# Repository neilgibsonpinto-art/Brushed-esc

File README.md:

# STMESC - Dual-Motor Brushed Electronic Speed Controller

[-green.svg)](https://www.st.com)
[-orange.svg)](#power-specifications)

**STMESC** is an open-source, high-power dual-channel electronic speed controller designed to drive **two DC brushed motors independently** (up to 15 A per channel) from a **3S to 6S LiPo battery (9.0 V – 25.2 V)**. 

Powered by a **240 MHz dual-core ESP32**, the STMESC features **Tri-Mode Hybrid Control** (Bluetooth LE, Wi-Fi, and standard hobby RC), onboard reverse polarity protection, real-time current sensing with stall detection, and an integrated 5 V / 2 A switching BEC. It is ideally suited for combat robotics, differential-drive rovers, smart RC models, and automation platforms.

---

## 📸 Hardware Previews

<div align="center">
  
  &nbsp;
  
</div>

---

## 🌟 Key Features

* **Dual Independent 15 A H-Bridges**: Dual automotive-grade **STMicroelectronics VNH7070BASTR** drivers with integrated power MOSFETs, charge pumps, and diagnostic logic.
* **3S to 6S LiPo Voltage Range ($9.0\text{ V} - 25.2\text{ V}$)**: Wide input voltage support compatible with 3S ($11.1\text{ V}$), 4S ($14.8\text{ V}$), and 6S ($22.2\text{ V}$) packs.
* **Ultrasonic PWM Drive**: Hardware PWM up to $20\text{ kHz}$ for smooth, responsive, and completely silent motor operation (no high-pitch whine).
* **Tri-Mode Hybrid Connectivity**:
  1. **Bluetooth Low Energy (BLE)**: Low-latency smartphone and gamepad control with live telemetry.
  2. **Wi-Fi Web Dashboard**: Built-in access point and HTTP/WebSocket server for control from any browser without installing an app.
  3. **RC Receiver Input**: Direct hardware pulse decoding for FlySky, FrSky, RadioMaster, ELRS, and Spektrum transmitters.
* **Real-Time Current Sensing & Stall Protection**: Dedicated ST MultiSense current feedback ($K_{sense} \approx 2000$) on both channels for active stall detection and overcurrent limiting.
* **Active Reverse Polarity Protection**: Low-$R_{DS(on)}$ P-Channel MOSFET with Zener gate clamp prevents board destruction if battery leads are reversed.
* **Integrated Dual Power Supply**:
  - **$5.0\text{ V} \text{ @ } 2.0\text{ A}$ Synchronous Buck Converter** (`U6`: AP63205) powers external receivers and sensors.
  - **$3.3\text{ V} \text{ @ } 1.0\text{ A}$ Low-Dropout Linear Regulator** (`U5`: AMS1117-3.3) powers the ESP32 and logic circuitry.
* **Developer & Maker Friendly**: Standard 6-pin UART programming header with auto-bootloader control, on-board tactile buttons (Reset, Boot, Mode), and diagnostic status LEDs.

---

## 📐 System Architecture

```mermaid
flowchart TD
    subgraph PowerStage ["Power Management (3S-6S LiPo: 9V - 25.2V)"]
        BAT["Battery Input J5\n(5.08mm Terminal)"] --> RP["Reverse Polarity Protection\n(Q2 P-MOSFET + D3 15V Zener)"]
        RP --> VCC["Main Rail (VCC: 9V - 25.2V)"]
        VCC --> BUCK["5V 2A Buck Regulator\n(U6: AP63205)"]
        BUCK --> LDO["3.3V 1A LDO Regulator\n(U5: AMS1117-3.3)"]
    end

    subgraph MCU ["Controller Brain (ESP32-WROOM-32E)"]
        LDO --> ESP["ESP32 Dual-Core @ 240MHz"]
        SW["Mode Select Switch (SW3)"] --> ESP
        LEDS["Status LEDs (D1, D4, D5)"] <-- ESP
    end

    subgraph Inputs ["Tri-Mode Control Inputs"]
        BLE["Mode 1: Bluetooth LE\n(Phone App / Gamepad)"] -.-> ESP
        WIFI["Mode 2: Wi-Fi\n(Web Dashboard / Telemetry)"] -.-> ESP
        RC["Mode 3: RC Receiver Header J6\n(Dual Channel PWM / PPM)"] --> ESP
    end

    subgraph MotorDrivers ["Dual ST VNH7070BASTR Drivers"]
        VCC --> U1["Driver 1: Motor 1 (U1)"]
        VCC --> U2["Driver 2: Motor 2 (U2)"]
        
        ESP -- "PWM1, INA1, INB1" --> U1
        ESP -- "PWM2, INA2, INB2" --> U2
        
        U1 -- "MultiSense Current" --> CS1["Current Filter (ADC1_CH1)"] --> ESP
        U2 -- "MultiSense Current" --> CS2["Current Filter (ADC1_CH2)"] --> ESP
        
        U1 --> M1["Motor 1 Output (J2)"]
        U2 --> M2["Motor 2 Output (J3)"]
    end
```

---

## 🔌 Pinout & Connector Specifications

### Power & Motor Terminals (5.08 mm Screw Blocks)
| Connector | Pin | Net Name | Description |
| :--- | :---: | :--- | :--- |
| **`J5`** | 1 | `VABT` | Battery Positive Input ($+9.0\text{ V}$ to $+25.2\text{ V}$) |
| | 2 | `GND` | Battery Negative / Power Ground |
| **`J2`** | 1, 2 | `Net-(J2-Pin_1)`, `Net-(J2-Pin_2)` | Motor 1 Phase Outputs (Bi-directional, up to 15 A) |
| **`J3`** | 1, 2 | `Net-(J3-Pin_1)`, `Net-(J3-Pin_2)` | Motor 2 Phase Outputs (Bi-directional, up to 15 A) |

### Control & Interface Headers
| Header | Pin | Signal | ESP32 GPIO | Description |
| :--- | :---: | :--- | :---: | :--- |
| **`J4` (UART)** | 1 | `+3V3` | - | 3.3 V Power (from onboard LDO) |
| | 2 | `/MCU_TXD` | GPIO1 | ESP32 UART0 Transmit |
| | 3 | `/MCU_RXD` | GPIO3 | ESP32 UART0 Receive |
| | 4 | `/MCU_IO0` | GPIO0 | Bootloader strapping pin (active LOW) |
| | 5 | `/MCU_EN` | EN | Microcontroller Enable / Reset (active LOW) |
| | 6 | `GND` | GND | Logic Ground |
| **`J6` (RC In)** | 1 | `/RC_IN1` | GPIO18 | Channel 1 RC pulse input (Throttle / Motor 1) |
| | 2 | `/RC_IN2` | GPIO16 | Channel 2 RC pulse input (Steering / Motor 2) |
| | 3, 4 | `+5V` | - | $+5.0\text{ V}$ BEC Output (powers external RC receiver) |
| | 5, 6 | `GND` | - | Receiver Ground |

### Tactile Switches & Status Indicators
| Component | Connected To | Function |
| :--- | :--- | :--- |
| **`SW1`** | `EN` / Reset | Hardware reset push button |
| **`SW2`** | `GPIO0` / Boot | Firmware flash bootloader button |
| **`SW3`** | `GPIO4` | Control Mode cycle switch (BLE $\leftrightarrow$ Wi-Fi $\leftrightarrow$ RC) |
| **`D1`** | `GPIO23` | Status Indicator LED 1 |
| **`D4`** | `GPIO21` | Mode Indicator LED 2 |
| **`D5`** | `GPIO22` | Fault / Diagnostic Alert LED 3 |

---

## 🕹️ Motor Truth Table

The ESP32 controls the ST VNH7070 drivers using **`INA`**, **`INB`**, and **`PWM`** logic signals:

| State | INA | INB | PWM | OUTA | OUTB | Motor Action |
| :--- | :---: | :---: | :---: | :---: | :---: | :--- |
| **Forward** | **HIGH** | **LOW** | **PWM %** | $V_{CC}$ (Chopped) | GND | Motor rotates forward; speed proportional to PWM duty cycle |
| **Reverse** | **LOW** | **HIGH** | **PWM %** | GND | $V_{CC}$ (Chopped) | Motor rotates reverse; speed proportional to PWM duty cycle |
| **Brake** | **LOW** | **LOW** | **HIGH** | GND | GND | Dynamic braking: low-side FETs short motor back-EMF |
| **Coast** | **LOW** | **LOW** | **LOW** | High-Z | High-Z | All MOSFETs disabled; motor freewheels to a stop |

---

## 📊 Technical Specifications

| Parameter | Specification |
| :--- | :--- |
| **PCB Form Factor** | $55.0\text{ mm} \times 45.0\text{ mm}$ (2-Layer FR-4, $1.6\text{ mm}$ thickness) |
| **Nominal Input Voltage** | $9.0\text{ V} - 25.2\text{ V}$ (3S, 4S, 5S, 6S LiPo / Li-ion) |
| **Max Continuous Current** | 10 A – 15 A peak per motor channel |
| **BEC Output** | $5.0\text{ V} \text{ @ } 2.0\text{ A}$ (Synchronous Step-Down Buck) |
| **Logic Voltage** | $3.3\text{ V}$ |
| **Current Sense Scale** | ST MultiSense $K_{sense} \approx 2000$ ($I_{sense} = I_{motor} / 2000$) |
| **Supported RC Receivers** | Standard $50\text{ Hz}$ PWM / PPM ($1000\ \mu\text{s} - 2000\ \mu\text{s}$) |
| **Wireless Protocols** | Wi-Fi 802.11 b/g/n (2.4 GHz) & Bluetooth v4.2 BR/EDR and BLE |
| **CAD Environment** | KiCad 10.0+ |

---

## 🗂️ Repository Structure

```text
├── docs/
│   ├── STMESC_Comprehensive_Verification_Report.pdf  # Detailed circuit & DRC audit report
│   └── images/
│       ├── pcb_render.png                            # High-resolution PCB layout render
│       └── sch_render.png                            # High-resolution schematic export
├── enclosure/
│   ├── README.md                                     # Enclosure specifications & print guide
│   ├── stmesc_enclosure.scad                         # Parametric OpenSCAD 3D printable model
│   └── stmesc_enclosure_fusion/                      # Fusion 360 script & CAD manifest
├── manufacturing/
│   └── gerbers/                                      # Production-ready Gerbers & Drill files
├── scripts/
│   └── run_all_tests_and_generate_report.py          # Automated KiCad ERC/DRC verification suite
├── stmesc.kicad_pro                                  # KiCad 10 Project file
├── stmesc.kicad_sch                                  # KiCad 10 Schematic sheet
├── stmesc.kicad_pcb                                  # KiCad 10 PCB layout
├── stmesc.kicad_sym                                  # Project symbol library
├── stmesc.csv                                        # Bill of Materials (BOM) with supplier links
├── stmesc.step                                       # 3D STEP CAD model of assembled PCB
├── .gitignore                                        # Comprehensive KiCad & Python gitignore
├── CONTRIBUTING.md                                   # Contribution guidelines
├── LICENSE                                           # MIT Open Source License
└── README.md                                         # Main documentation
```

---

## 📦 Bill of Materials (Key Components)

| Designator | Value / Part Number | Description | Package | Supplier Reference |
| :--- | :--- | :--- | :--- | :--- |
| **`U1, U2`** | VNH7070BASTR | Dual 15 A Automotive H-Bridge Motor Driver | SOIC-16N | [STMicroelectronics](https://www.st.com) |
| **`U3`** | ESP32-WROOM-32E | Dual-Core 240 MHz Wi-Fi/BLE MCU Module | SMD Module | [Espressif](https://espressif.com) |
| **`U6`** | AP63205WU-7 | 2 A 5 V Synchronous Buck Converter | TSOT-26 | [Diodes Inc](https://www.diodes.com) |
| **`U5`** | AMS1117-3.3 | 1 A 3.3 V Low-Dropout Linear Regulator | SOT-223-3 | Standard OSHW |
| **`Q2`** | SUD50P04-08 / IRFR5305 | -40V / -55V P-Channel Reverse Polarity MOSFET | TO-252 (DPAK) | Vishay / Infineon |
| **`D3`** | BZT52C15-7-F | 15 V 500 mW Zener Gate Protection Diode | SOD-123 | Diodes Inc |
| **`L1`** | 4.7 µH 3 A | Shielded Power Inductor (SWPA5040S) | 5.0x5.0 mm | Sunlord |
| **`C1, C2`** | 220 µF / 270 µF 35 V | Low-ESR SMD Aluminum Electrolytic Capacitor | 8x10.5 mm | Nichicon / Panasonic |
| **`J2, J3, J5`** | MKDS 1,5/2-5.08 | 2-Pin 5.08 mm Pitch Heavy-Duty Screw Terminal | 5.08 mm TH | Phoenix Contact |
| **`SW1-SW3`** | TS-1088-xR025 | SMD Tactile Push Button Switches | 3.9x3.0 mm | Standard SMD |

---

## 🧪 Automated Verification & Testing

This project includes a Python-based automated verification suite located in `scripts/run_all_tests_and_generate_report.py`. It integrates with `kicad-cli` to perform:
1. KiCad Electrical Rules Check (ERC).
2. Design Rules Check (DRC) with tolerance verification.
3. High-current trace thermal ampacity calculations (IPC-2221).
4. ESP32 2.4 GHz antenna keepout clearance checking.
5. Component BOM procurement and distributor availability audit.
6. Automatic generation of `docs/STMESC_Comprehensive_Verification_Report.pdf`.

To run the verification suite locally:
```bash
python scripts/run_all_tests_and_generate_report.py
```

---

## 📄 License

This hardware design and associated software/firmware tools are released under the [MIT License](LICENSE).
Feel free to use, modify, and build upon this design for your personal, educational, or commercial robotics projects!

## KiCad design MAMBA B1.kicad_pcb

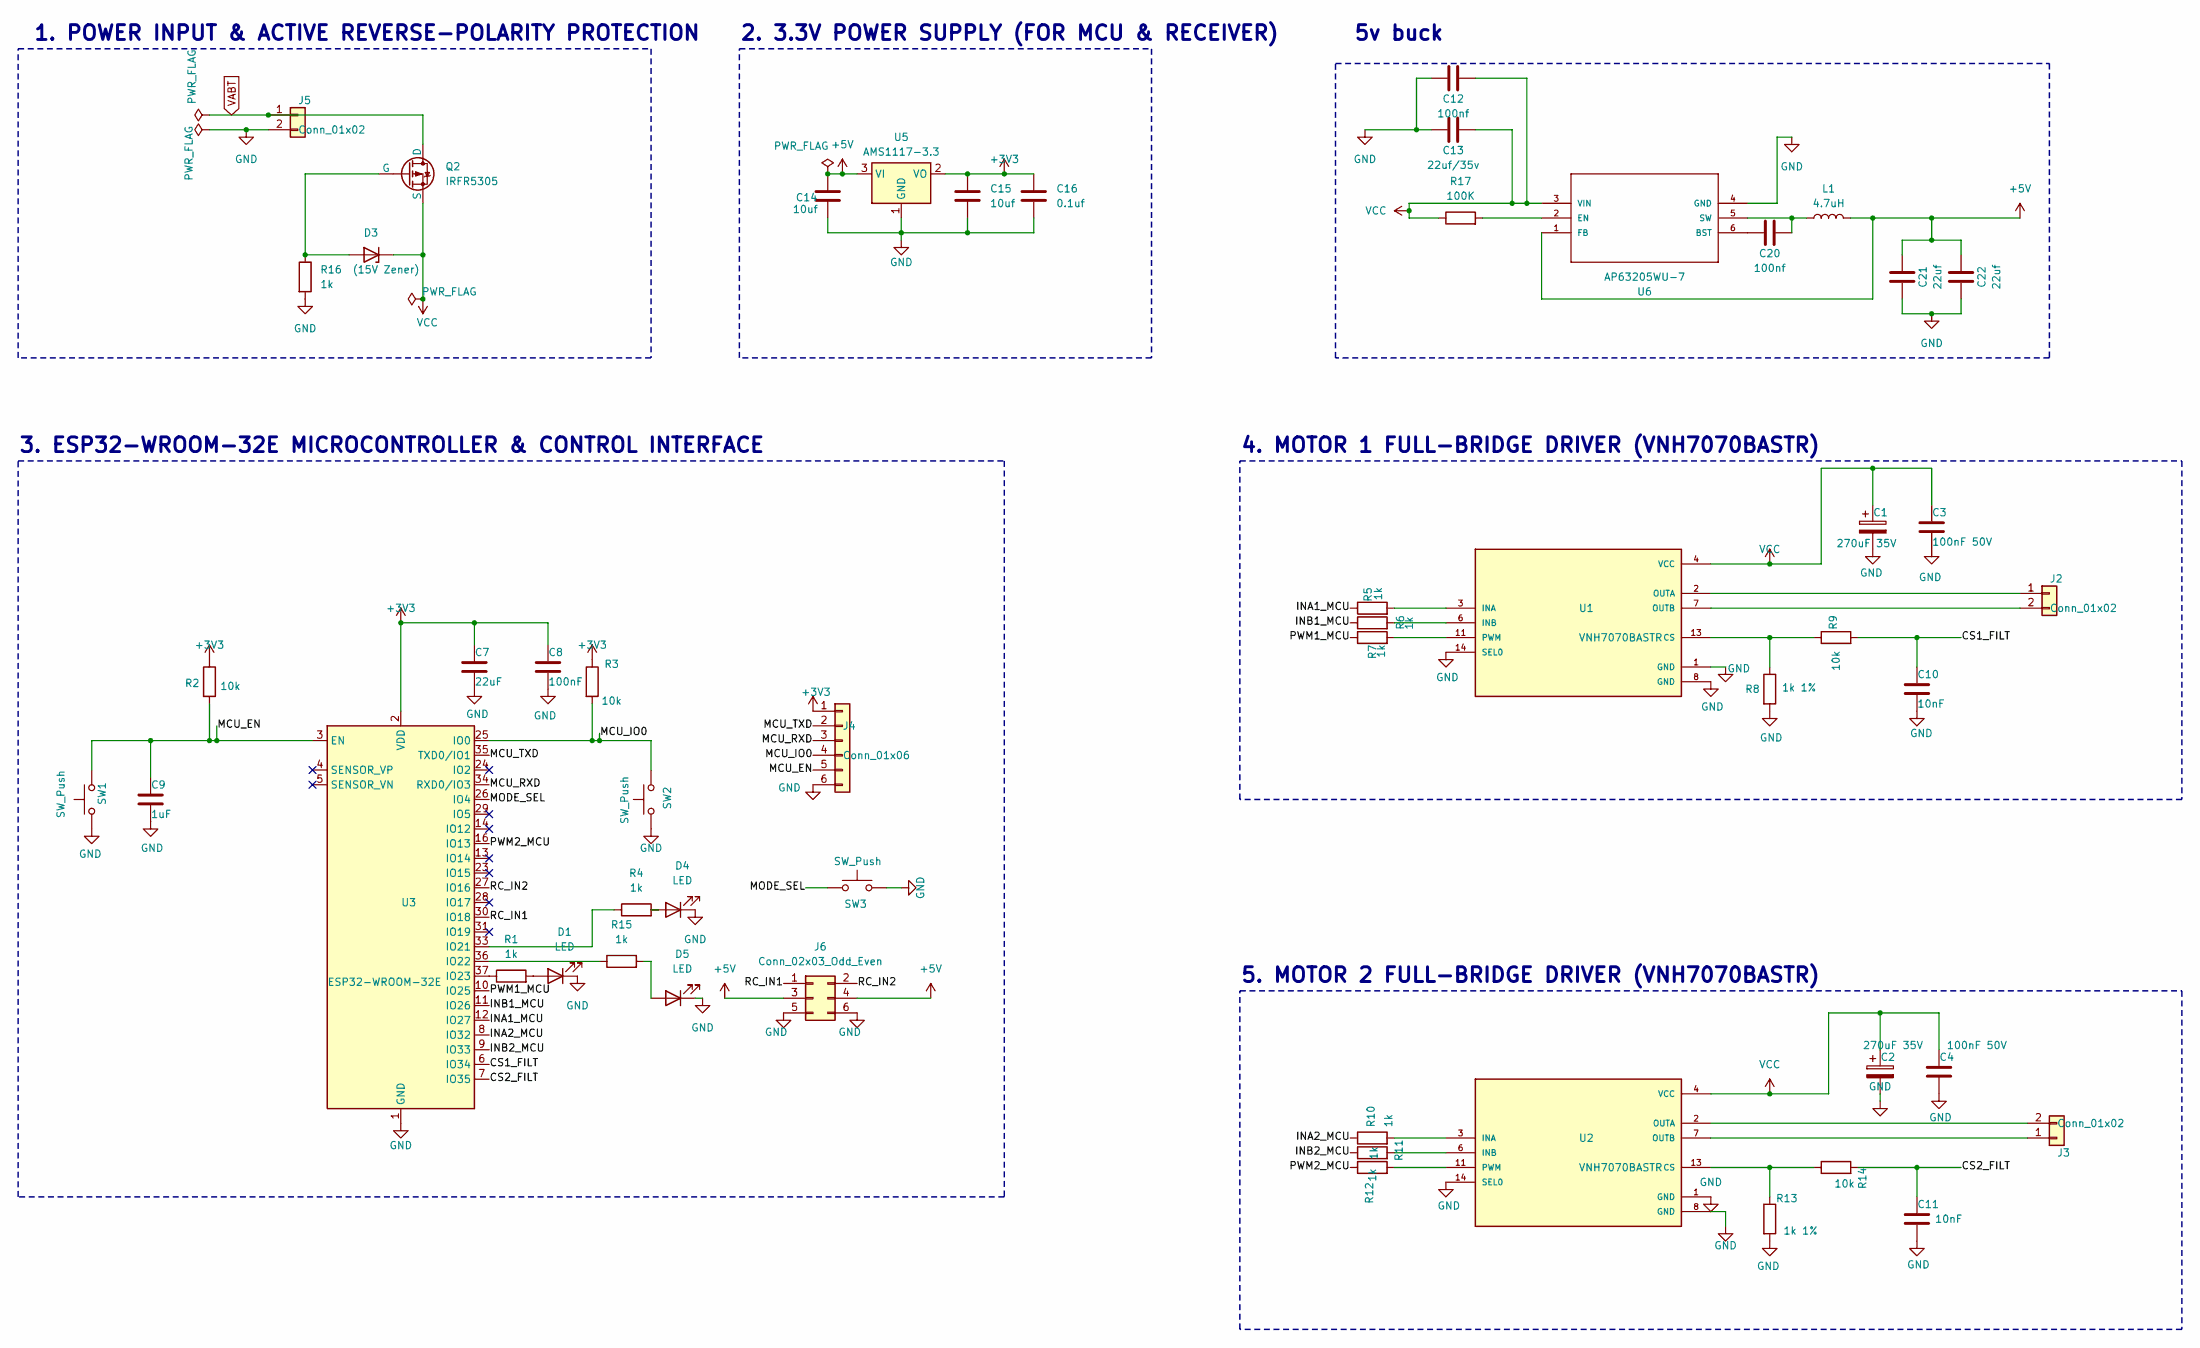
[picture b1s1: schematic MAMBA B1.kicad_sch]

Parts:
C1, C2: 270uF 35V; CP_Elec_8x10.5
C3, C4: 100nF 50V; C_0805_2012Metric_Pad1.18x1.45mm_HandSolder
C7: 22uF; C_1206_3216Metric
C8: 100nF; C_0805_2012Metric_Pad1.18x1.45mm_HandSolder
C9: 1uF; C_0805_2012Metric_Pad1.18x1.45mm_HandSolder
C10, C11: 10nF; C_0805_2012Metric_Pad1.18x1.45mm_HandSolder
C12, C20: 100nf; C_0805_2012Metric_Pad1.18x1.45mm_HandSolder
C13: 22uf/35v; C_1206_3216Metric_Pad1.33x1.80mm_HandSolder
C14, C15: 10uf; C_0805_2012Metric_Pad1.18x1.45mm_HandSolder
C16: 0.1uf; C_0805_2012Metric_Pad1.18x1.45mm_HandSolder
C21, C22: 22uf; C_1206_3216Metric_Pad1.33x1.80mm_HandSolder
D1, D4, D5: LED; LED_0805_2012Metric
D3: (15V Zener); D_SOD-123
J2, J3, J5: Conn_01x02; TerminalBlock_Phoenix_MKDS-1,5-2-5.08_1x02_P5.08mm_Horizont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
J4: Conn_01x06; PinHeader_1x06_P2.54mm_Vertical
J6: Conn_02x03_Odd_Even; PinHeader_2x03_P2.54mm_Vertical
L1: 4.7uH; L_Sunlord_SWPA5040S
Q2: IRFR5305; TO-252-2
R1, R4, R5, R6, R7, R10, R11, R12, R15, R16: 1k; R_0805_2012Metric_Pad1.20x1.40mm_HandSolder
R2, R3, R9, R14: 10k; R_0805_2012Metric_Pad1.20x1.40mm_HandSolder
R8, R13: 1k 1%; R_0805_2012Metric_Pad1.20x1.40mm_HandSolder
R17: 100K; R_0805_2012Metric_Pad1.20x1.40mm_HandSolder
SW1, SW2: SW_Push; SW_SPST_TS-1088-xR025
SW3: SW_Push; SW_PUSH_6mm
U1, U2: VNH7070BASTR; SOIC-16_3.9x9.9mm_P1.27mm
U3: ESP32-WROOM-32E; ESP32-WROOM-32D
U5: AMS1117-3.3; SOT-223-3_TabPin2
U6: AP63205WU-7; SOIC_05WU-7_DIO-M; MPN AP63205WU-7

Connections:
+3V3: C7.1, C8.1, C15.1, C16.1, J4.1, R2.1, R3.1, U3.2 (VDD), U5.2 (VO)
+5V: C14.1, C21.2, C22.2, J6.3, J6.4, L1.2, U5.3 (VI), U6.1 (FB)
/CS1_FILT: C10.1, R9.2, U3.6 (IO34)
/CS2_FILT: C11.1, R14.2, U3.7 (IO35)
/INA1_MCU: R5.1, U3.12 (IO27)
/INA2_MCU: R10.1, U3.8 (IO32)
/INB1_MCU: R6.1, U3.11 (IO26)
/INB2_MCU: R11.1, U3.9 (IO33)
/MCU_EN: C9.1, J4.5, R2.2, SW1.2, U3.3 (EN)
/MCU_IO0: J4.4, R3.2, SW2.2, U3.25 (IO0)
/MCU_RXD: J4.3, U3.34 (RXD0/IO3)
/MCU_TXD: J4.2, U3.35 (TXD0/IO1)
/MODE_SEL: SW3.2, U3.26 (IO4)
/PWM1_MCU: R7.1, U3.10 (IO25)
/PWM2_MCU: R12.1, U3.16 (IO13)
/RC_IN1: J6.1, U3.30 (IO18)
/RC_IN2: J6.2, U3.27 (IO16)
unnamed: D1.2 (A), R1.2
unnamed: D3.2 (A), Q2.1 (G), R16.1
unnamed: D4.2 (A), R4.2
unnamed: D5.2 (A), R15.2
unnamed: J2.1, U1.2 (OUTA), U1.15 (OUTA)
unnamed: J2.2, U1.7 (OUTB), U1.10 (OUTB)
unnamed: J3.1, U2.7 (OUTB), U2.10 (OUTB)
unnamed: J3.2, U2.2 (OUTA), U2.15 (OUTA)
unnamed: R8.1, R9.1, U1.13 (CS)
unnamed: R5.2, U1.3 (INA)
unnamed: R6.2, U1.6 (INB)
unnamed: R7.2, U1.11 (PWM)
unnamed: R13.1, R14.1, U2.13 (CS)
unnamed: R10.2, U2.3 (INA)
unnamed: R11.2, U2.6 (INB)
unnamed: R12.2, U2.11 (PWM)
unnamed: R4.1, U3.33 (IO21)
unnamed: R15.1, U3.36 (IO22)
unnamed: R1.1, U3.37 (IO23)
unnamed: C20.1, U6.6 (BST)
unnamed: R17.2, U6.2 (EN)
unnamed: C20.2, L1.1, U6.5 (SW)

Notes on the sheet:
5. MOTOR 2 FULL-BRIDGE DRIVER (VNH7070BASTR)
4. MOTOR 1 FULL-BRIDGE DRIVER (VNH7070BASTR)
2. 3.3V POWER SUPPLY (FOR MCU & RECEIVER)
3. ESP32-WROOM-32E MICROCONTROLLER & CONTROL INTERFACE
5v buck
1. POWER INPUT & ACTIVE REVERSE-POLARITY PROTECTION

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
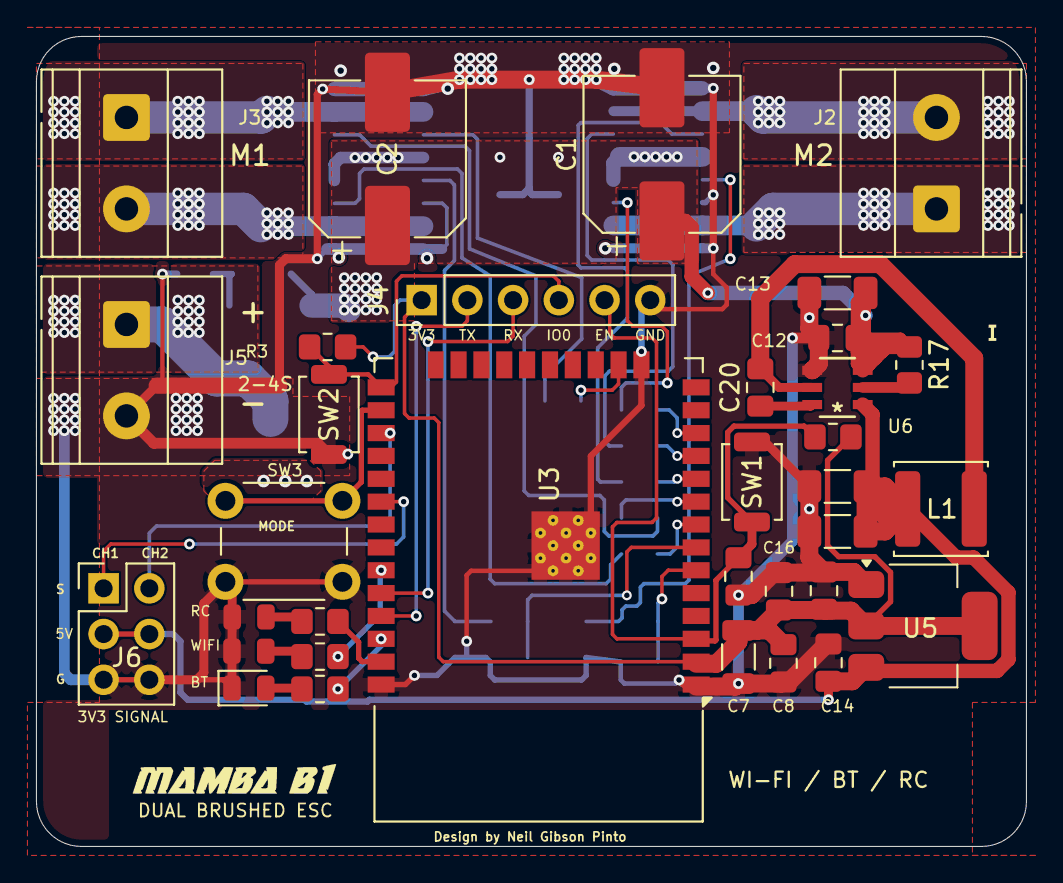
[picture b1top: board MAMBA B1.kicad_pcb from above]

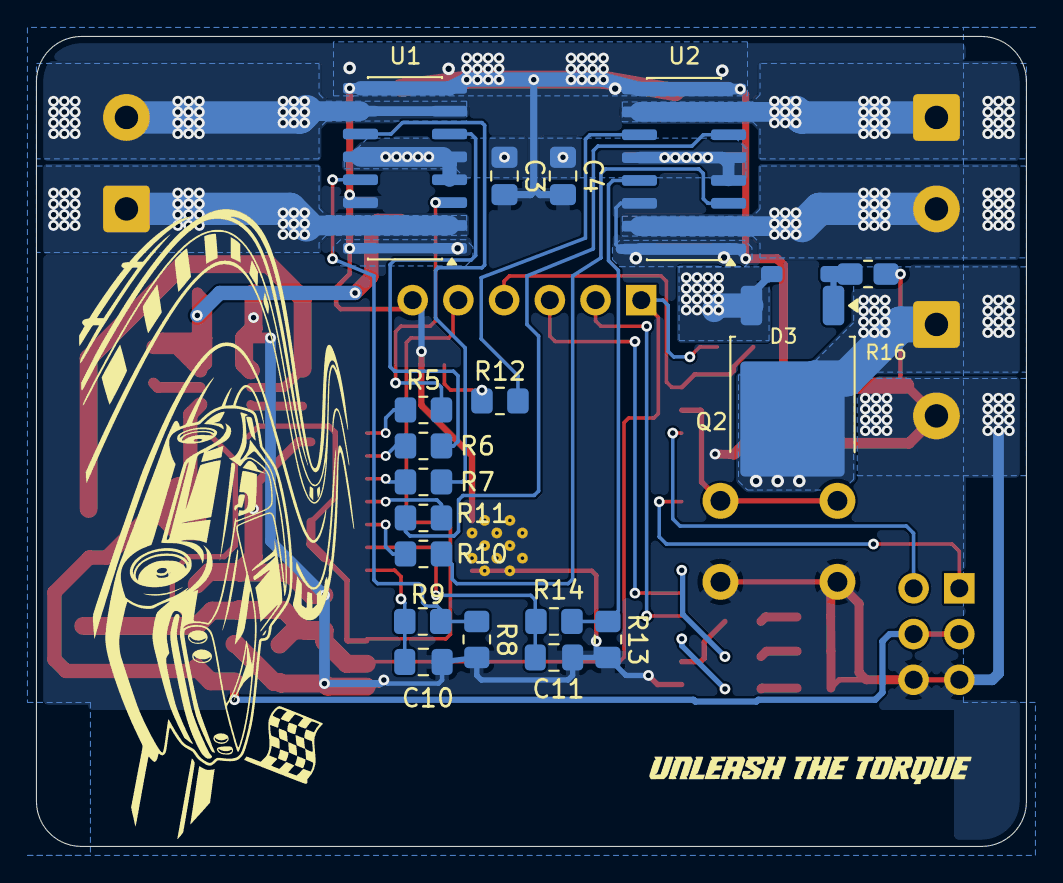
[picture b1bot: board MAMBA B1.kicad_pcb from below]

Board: 2 copper layers, 55.0 x 45.0 mm, 53 parts (19 on the bottom side), 42 nets.

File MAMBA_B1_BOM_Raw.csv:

"Designator","Value","Footprint","Quantity"
"C1,C2","270uF 35V","Capacitor_SMD:CP_Elec_8x10.5","2"
"C3,C4","100nF 50V","Capacitor_SMD:C_0805_2012Metric_Pad1.18x1.45mm_HandSolder","2"
"C7","22uF","Capacitor_SMD:C_1206_3216Metric","1"
"C8","100nF","Capacitor_SMD:C_0805_2012Metric_Pad1.18x1.45mm_HandSolder","1"
"C9","1uF","Capacitor_SMD:C_0805_2012Metric_Pad1.18x1.45mm_HandSolder","1"
"C10,C11","10nF","Capacitor_SMD:C_0805_2012Metric_Pad1.18x1.45mm_HandSolder","2"
"C12,C20","100nf","Capacitor_SMD:C_0805_2012Metric_Pad1.18x1.45mm_HandSolder","2"
"C13","22uf/35v","Capacitor_SMD:C_1206_3216Metric_Pad1.33x1.80mm_HandSolder","1"
"C14,C15","10uf","Capacitor_SMD:C_0805_2012Metric_Pad1.18x1.45mm_HandSolder","2"
"C16","0.1uf","Capacitor_SMD:C_0805_2012Metric_Pad1.18x1.45mm_HandSolder","1"
"C21,C22","22uf","Capacitor_SMD:C_1206_3216Metric_Pad1.33x1.80mm_HandSolder","2"
"D1,D4,D5","LED","LED_SMD:LED_0805_2012Metric","3"
"D3","(15V Zener)","Diode_SMD:D_SOD-123","1"
"J2,J3,J5","Conn_01x02","TerminalBlock_Phoenix:TerminalBlock_Phoenix_MKDS-1,5-2-5.08_1x02_P5.08mm_Horizontal","3"
"J4","Conn_01x06","Connector_PinHeader_2.54mm:PinHeader_1x06_P2.54mm_Vertical","1"
"J6","Conn_02x03_Odd_Even","Connector_PinHeader_2.54mm:PinHeader_2x03_P2.54mm_Vertical","1"
"L1","4.7uH","Inductor_SMD:L_Sunlord_SWPA5040S","1"
"Q2","IRFR5305","Package_TO_SOT_SMD:TO-252-2","1"
"R1,R4-R7,R10-R12,R15,R16","1k","Resistor_SMD:R_0805_2012Metric_Pad1.20x1.40mm_HandSolder","10"
"R2,R3,R9,R14","10k","Resistor_SMD:R_0805_2012Metric_Pad1.20x1.40mm_HandSolder","4"
"R8,R13","1k 1%","Resistor_SMD:R_0805_2012Metric_Pad1.20x1.40mm_HandSolder","2"
"R17","100K","Resistor_SMD:R_0805_2012Metric_Pad1.20x1.40mm_HandSolder","1"
"SW1,SW2","SW_Push","Button_Switch_SMD:SW_SPST_TS-1088-xR025","2"
"SW3","SW_Push","Button_Switch_THT:SW_PUSH_6mm","1"
"U1,U2","VNH7070BASTR","Package_SO:SOIC-16_3.9x9.9mm_P1.27mm","2"
"U3","ESP32-WROOM-32E","RF_Module:ESP32-WROOM-32D","1"
"U5","AMS1117-3.3","Package_TO_SOT_SMD:SOT-223-3_TabPin2","1"
"U6","AP63205WU-7","neil:SOIC_05WU-7_DIO-M","1"

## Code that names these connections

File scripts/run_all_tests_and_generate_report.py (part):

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        })

    # Test E: High-Current Motor Trace Width & Thermal Ampacity
    motor_nets = ['Net-(J2-Pin_1)', 'Net-(J2-Pin_2)', 'Net-(J3-Pin_1)', 'Net-(J3-Pin_2)', 'VABT', 'Net_VABT']
    motor_tracks = [s for s in segments if any(mn in s['net'] for mn in motor_nets)]
    max_w = max([s['width'] for s in motor_tracks]) if motor_tracks else 1.0
    if max_w <= 1.0:
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    errors_p2 = [
        {
            'num': 'ERROR 1 (CRITICAL BLOCKER)',
            'title': 'Reverse Polarity P-Channel MOSFET (Q2) Pinout & Gate Hardwired to VABT',
            'desc': (
                "- Exact Netlist Connection:\n"
                "  * Q2 Pin 1 (Gate) is wired directly to 'VABT' (Battery Positive Input J5.1).\n"
                "  * Q2 Pin 2 (Drain / Tab) is wired to 'Net-(D3-A)' which goes through R16 (1kOhm) to GND.\n"
                "  * Q2 Pin 3 (Source) is wired to 'VCC' (Internal Board Power Rail).\n"
                "  * Zener Diode D3 (15V) is across Drain (Pin 2) and Source (Pin 3).\n\n"
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                "  Therefore, Vgs is always >= 0V, and Q2 can NEVER turn ON under normal operation!\n"
                "  Furthermore, Drain is connected through 1kOhm to GND, drawing continuous quiescent current.\n\n"
                "- Actionable Correction Required:\n"
                "  1. Connect Q2 Source (Pin 3) to VABT (Battery Input J5.1).\n"
                "  2. Connect Q2 Drain (Pin 2 / Tab) to VCC (Internal System Rail).\n"
                "  3. Connect Q2 Gate (Pin 1) to GND through a 100kOhm pull-down resistor (R16).\n"
                "  4. Connect 15V Zener D3 between Gate (Pin 1, Anode) and Source (Pin 3, Cathode) to protect gate oxide from 6S voltage."
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            'title': '5V RC Receiver Signal Overvoltage on 3.3V ESP32 GPIO Inputs (J6 -> U3)',
            'desc': (
                "- Exact Netlist Connection:\n"
                "  * Header J6 Pin 1 (/RC_IN1) connects directly to ESP32 Pin 30 (GPIO18).\n"
                "  * Header J6 Pin 2 (/RC_IN2) connects directly to ESP32 Pin 27 (GPIO16).\n"
                "  * Header J6 Pins 3 & 4 provide +5V power to the external RC receiver.\n\n"
                "- Circuit Analysis & Failure Mode:\n"
                "  Standard hobby RC receivers (FrSky, FlySky, Futaba, Spektrum, ELRS) powered by +5V output 5.0V PWM/PPM pulses.\n"
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            'desc': (
                "- Exact Netlist Connection:\n"
                "  * U1 & U2 MultiSense outputs (Pin 13) connect across R8 & R13 (1kOhm 1% to GND).\n"
                "  * Filtered via R9 (10k) / C10 (10nF) to Net '/CS1_FILT' (ESP32 Pin 6 / SENSOR_CAPP / ADC1_CH1).\n"
                "  * Filtered via R14 (10k) / C11 (10nF) to Net '/CS2_FILT' (ESP32 Pin 7 / SENSOR_CAPN / ADC1_CH2).\n\n"
                "- Circuit Analysis & Failure Mode:\n"
                "  Per VNH7070BASTR datasheet, MultiSense current ratio is K_sense ~ 2000. Sense current I_sense = I_motor / 2000.\n"
                "  At rated motor current of 15A, I_sense = 15A / 2000 = 7.5mA.\n"
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    
    actions = [
        ("Step 1: Fix Reverse Polarity MOSFET (Q2)", "Swap Source/Drain on Q2: Source to VABT, Drain to VCC, Gate pulled to GND via 100kOhm with 15V Zener D3."),
        ("Step 2: Add 5V Level Shifting on RC Inputs (J6)", "Insert a 1.2kOhm/2.2kOhm resistor divider on RC_IN1 and RC_IN2 to protect ESP32 GPIOs from 5.0V receiver pulses."),
        ("Step 3: Rescale Motor Current Sense Shunts (R8/R13)", "Change R8 and R13 from 1kOhm to 330Ohm (1%) so 15A motor current maps to 2.48V on ESP32 ADC1 pins."),
        ("Step 4: Fix ESP32 Antenna RF Keepout", "Relocate ESP32 to overhang board edge by >=15mm or remove all copper/traces underneath the antenna."),
        ("Step 5: Increase Motor Copper Traces to 5.0mm+", "Replace 0.8mm-1.0mm traces on J2, J3, and VABT with wide polygon pours and dual-layer via stitching."),
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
